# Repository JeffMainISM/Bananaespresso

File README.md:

#  Bananaespresso

A small, fun build created during my first real steps into **3D design** and **KiCad** (coming from EasyEDA).  
It’s nothing more than a simple “U-shaped” pad — basic, slightly janky, but charming in its own way.  
Alignment might be *questionable*, but hey… if it works, it works!

This board does exactly what it needs to: **8 keys and 4 LEDs**.  
What else do you really need in life?

---

##  Overview

Not bad, right?

---

## PCB

The PCB is, uh… *a bit of an eyesore*.  
Messy? Yes. Functional? Also yes. And that’s what matters.

---

##  Bill of Materials (BOM)

| Qty | Item                     |
|----:|--------------------------|
| 8   | Cherry MX switches       |
| 8   | DSA keycaps              |
| 4   | WS2812B LEDs             |
| 1   | XIAO RP2040              |
| 1   | Case (2 printed parts)   |
| 4   | M3×16mm screws           |
| 4   | M3×5×4mm heat-set inserts|

---

##  Schematic

A simple, minimal schematic — but fairly clean for what it is.

---

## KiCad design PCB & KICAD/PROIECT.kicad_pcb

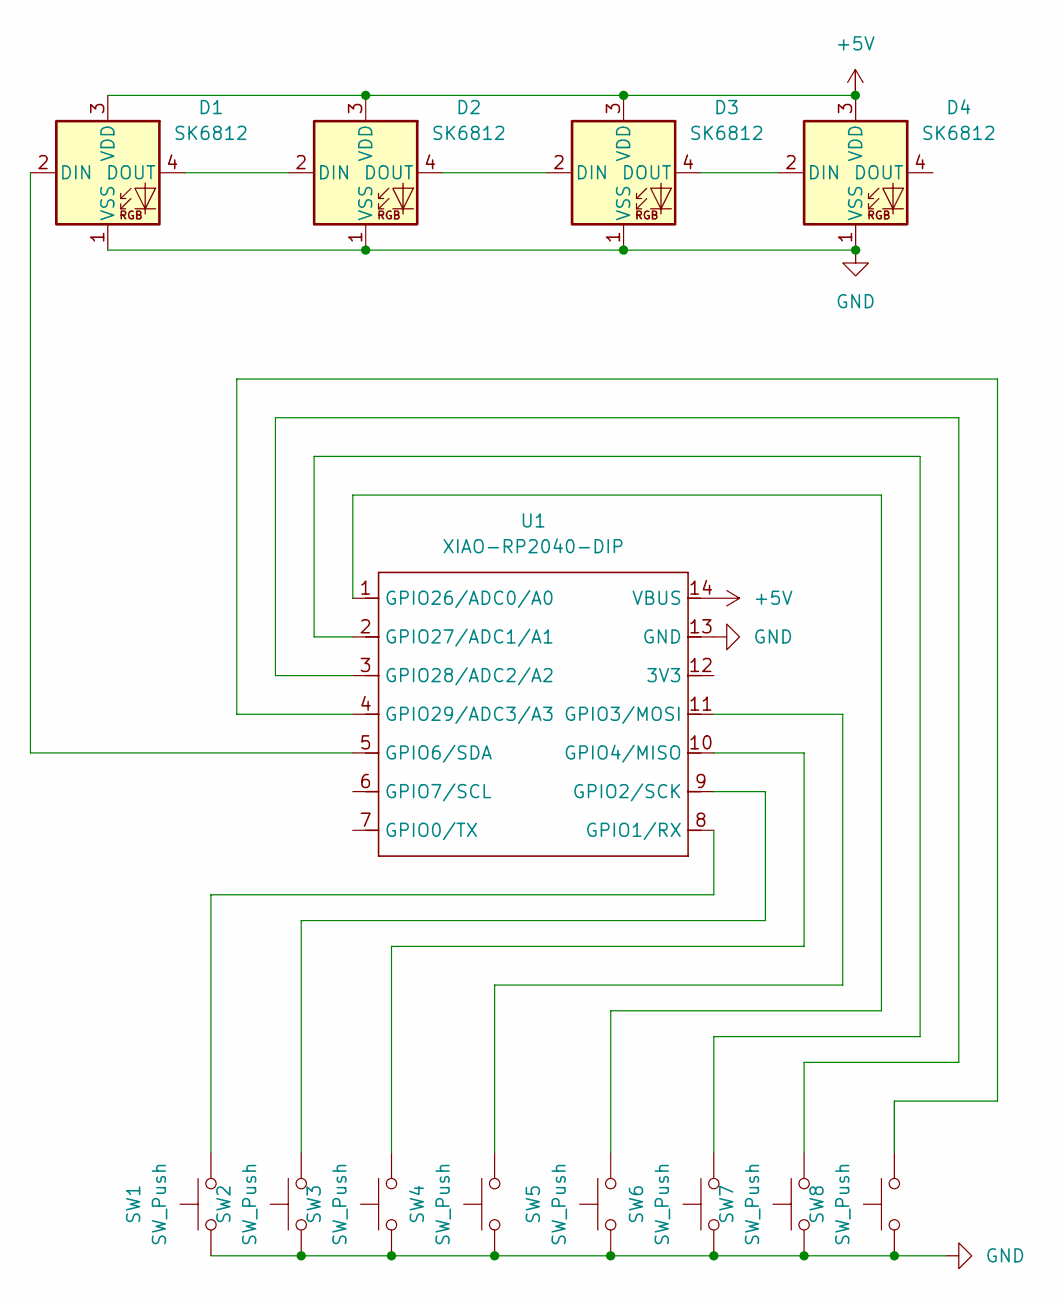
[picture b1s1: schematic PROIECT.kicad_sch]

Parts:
D1, D2, D3, D4: SK6812; LED_SK6812MINI_PLCC4_3.5x3.5mm_P1.75mm
SW1, SW2, SW3, SW4, SW5, SW6, SW7, SW8: SW_Push; SW_Cherry_MX_1.00u_PCB
U1: XIAO-RP2040-DIP

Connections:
+5V: D1.3 (VDD), D2.3 (VDD), D3.3 (VDD), D4.3 (VDD), U1.14 (VBUS)
GND: D1.1 (VSS), D2.1 (VSS), D3.1 (VSS), D4.1 (VSS), SW1.1, SW2.1, SW3.1, SW4.1, SW5.1, SW6.1, SW7.1, SW8.1, U1.13 (GND)
unnamed: D1.2 (DIN), U1.5 (GPIO6/SDA)
unnamed: D1.4 (DOUT), D2.2 (DIN)
unnamed: D2.4 (DOUT), D3.2 (DIN)
unnamed: D3.4 (DOUT), D4.2 (DIN)
unnamed: SW1.2, U1.8 (GPIO1/RX)
unnamed: SW2.2, U1.9 (GPIO2/SCK)
unnamed: SW4.2, U1.11 (GPIO3/MOSI)
unnamed: SW3.2, U1.10 (GPIO4/MISO)
unnamed: SW5.2, U1.1 (GPIO26/ADC0/A0)
unnamed: SW6.2, U1.2 (GPIO27/ADC1/A1)
unnamed: SW7.2, U1.3 (GPIO28/ADC2/A2)
unnamed: SW8.2, U1.4 (GPIO29/ADC3/A3)

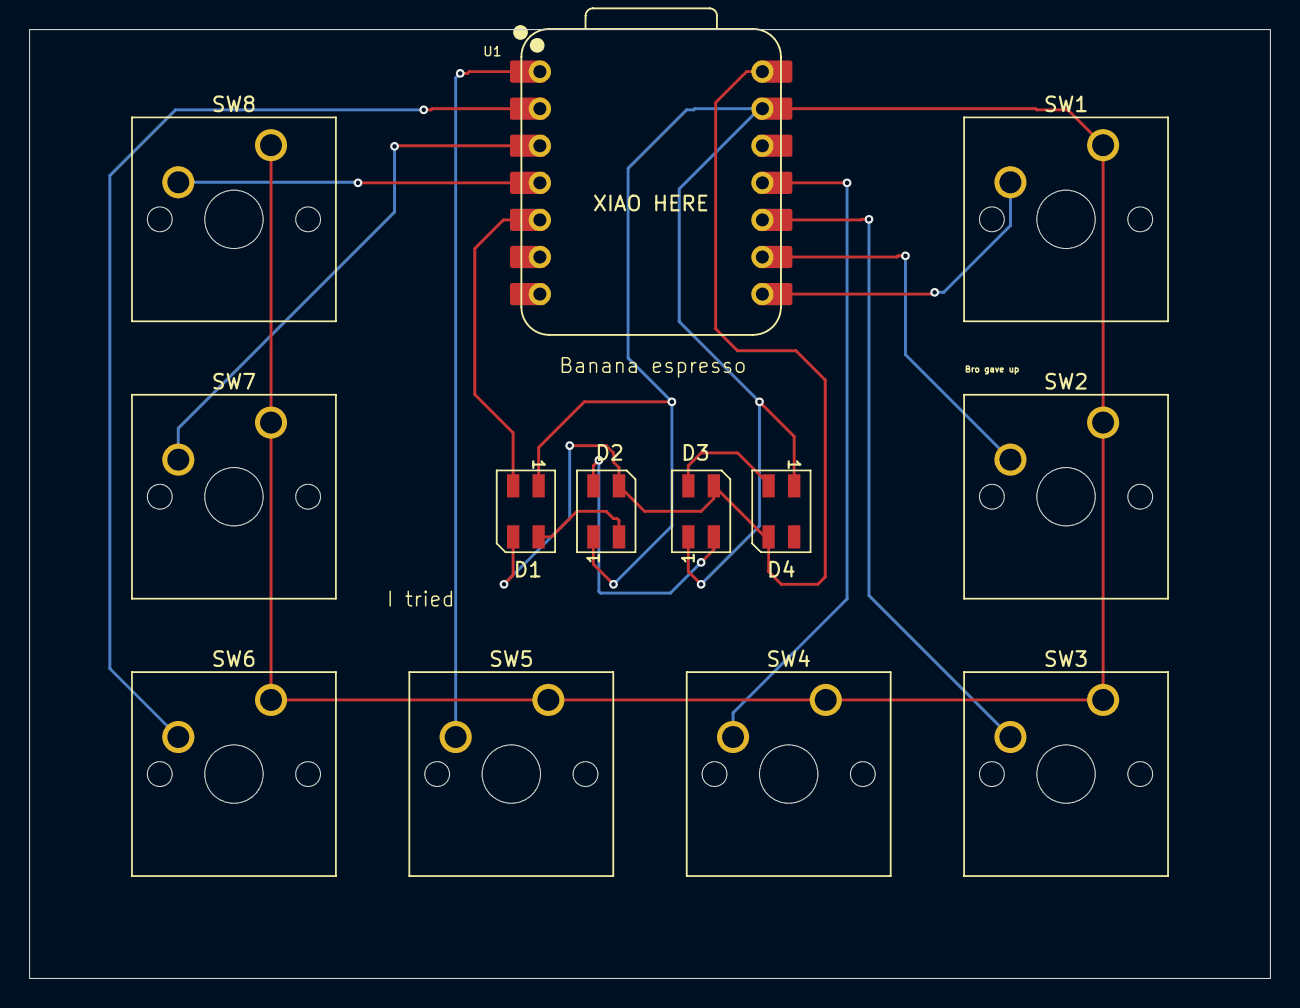
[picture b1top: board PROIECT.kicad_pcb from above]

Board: 2 copper layers, 85.0 x 65.0 mm, 13 parts (0 on the bottom side), 14 nets.

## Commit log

2025-12-04 Add files via upload
    This here? very banana.
2025-12-04 Create ex
2025-12-04 Rename ASAMBLAT.step to cad/ASAMBLAT.step
2025-12-04 Create e
2025-12-06 Create Photos
